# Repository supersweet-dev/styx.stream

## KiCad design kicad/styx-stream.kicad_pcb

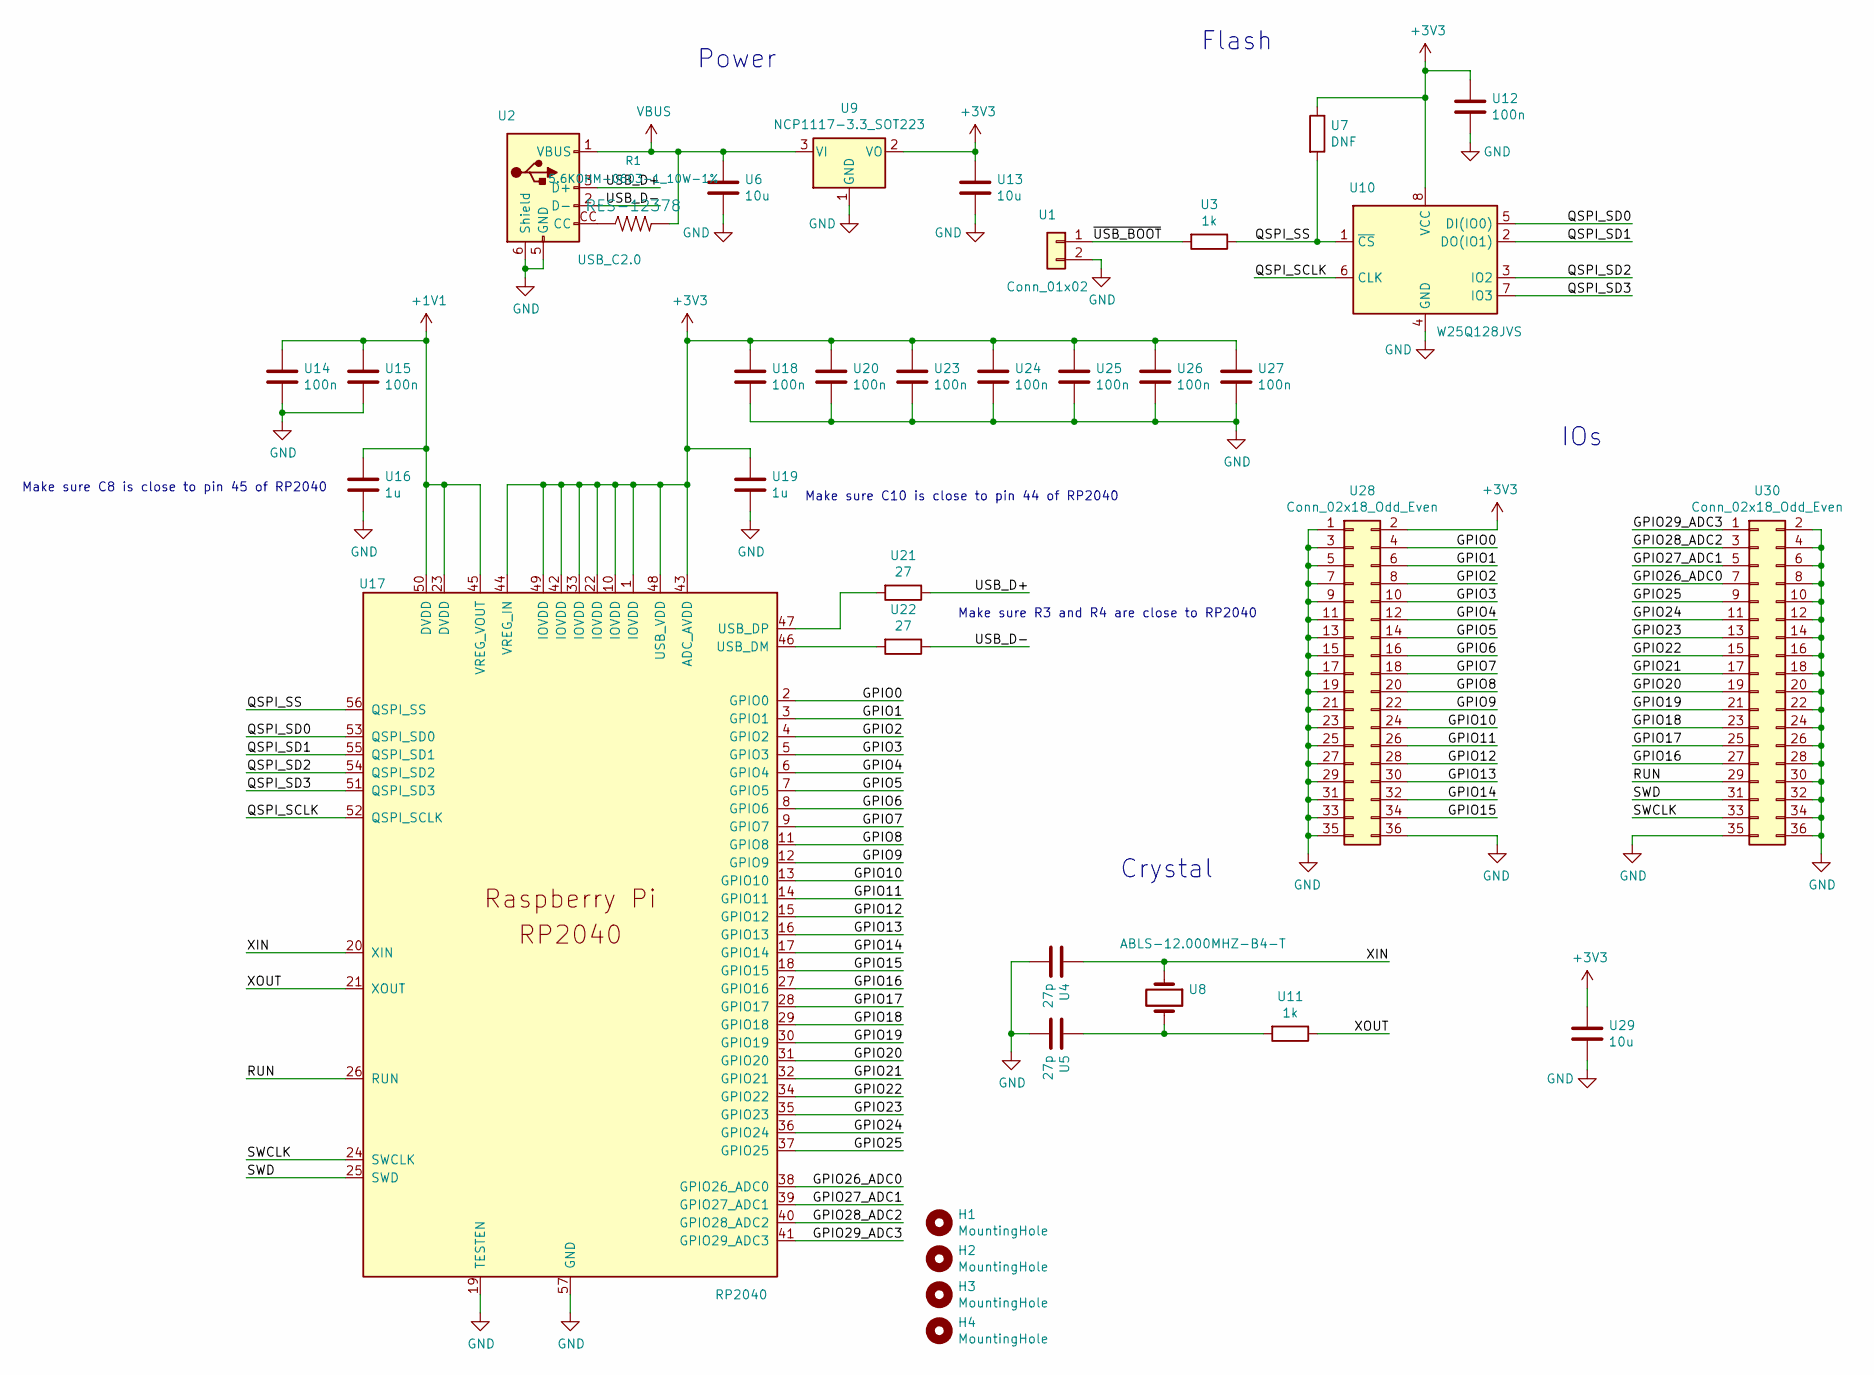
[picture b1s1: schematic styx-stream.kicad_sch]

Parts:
H1, H2, H3, H4: MountingHole; MountingHole_2.7mm_M2.5
R1: 5.6KOHM-0603-1_10W-1%; R_4020_10251Metric
U1: Conn_01x02; PinHeader_1x02_P2.54mm_Vertical
U2: USB_C2.0; USB_C_Receptacle_Amphenol_12401610E4-2A
U3, U11: 1k; C_0402_1005Metric
U4, U5: 27p; C_0402_1005Metric
U6, U13, U29: 10u; C_0805_2012Metric
U7: DNF; C_0402_1005Metric
U8: ABLS-12.000MHZ-B4-T; HC49UP
U9: NCP1117-3.3_SOT223; SOT-223-3_TabPin2
U10: W25Q128JVS; SOIC-8_5.23x5.23mm_P1.27mm
U12, U14, U15, U18, U20, U23, U24, U25, U26, U27: 100n; C_0402_1005Metric
U16, U19: 1u; C_0402_1005Metric
U17: RP2040; RP2040-QFN-56
U21, U22: 27; C_0402_1005Metric
U28, U30: Conn_02x18_Odd_Even; PinHeader_2x18_P2.54mm_Vertical

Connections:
+1V1: U14.1, U15.1, U16.1, U17.23 (DVDD), U17.45 (VREG_VOUT), U17.50 (DVDD)
+3V3: U7.1, U9.2 (VO), U10.8 (VCC), U12.1, U13.1, U17.1 (IOVDD), U17.10 (IOVDD), U17.22 (IOVDD), U17.33 (IOVDD), U17.42 (IOVDD), U17.43 (ADC_AVDD), U17.44 (VREG_IN), U17.48 (USB_VDD), U17.49 (IOVDD), U18.1, U19.1, U20.1, U23.1, U24.1, U25.1, U26.1, U27.1, U28.2, U29.1
/GPIO0: U17.2 (GPIO0), U28.4
/GPIO1: U17.3 (GPIO1), U28.6
/GPIO2: U17.4 (GPIO2), U28.8
/GPIO3: U17.5 (GPIO3), U28.10
/GPIO4: U17.6 (GPIO4), U28.12
/GPIO5: U17.7 (GPIO5), U28.14
/GPIO6: U17.8 (GPIO6), U28.16
/GPIO7: U17.9 (GPIO7), U28.18
/GPIO8: U17.11 (GPIO8), U28.20
/GPIO9: U17.12 (GPIO9), U28.22
/GPIO10: U17.13 (GPIO10), U28.24
/GPIO11: U17.14 (GPIO11), U28.26
/GPIO12: U17.15 (GPIO12), U28.28
/GPIO13: U17.16 (GPIO13), U28.30
/GPIO14: U17.17 (GPIO14), U28.32
/GPIO15: U17.18 (GPIO15), U28.34
/GPIO16: U17.27 (GPIO16), U30.27
/GPIO17: U17.28 (GPIO17), U30.25
/GPIO18: U17.29 (GPIO18), U30.23
/GPIO19: U17.30 (GPIO19), U30.21
/GPIO20: U17.31 (GPIO20), U30.19
/GPIO21: U17.32 (GPIO21), U30.17
/GPIO22: U17.34 (GPIO22), U30.15
/GPIO23: U17.35 (GPIO23), U30.13
/GPIO24: U17.36 (GPIO24), U30.11
/GPIO25: U17.37 (GPIO25), U30.9
/GPIO26_ADC0: U17.38 (GPIO26_ADC0), U30.7
/GPIO27_ADC1: U17.39 (GPIO27_ADC1), U30.5
/GPIO28_ADC2: U17.40 (GPIO28_ADC2), U30.3
/GPIO29_ADC3: U17.41 (GPIO29_ADC3), U30.1
/QSPI_SCLK: U10.6 (CLK), U17.52 (QSPI_SCLK)
/QSPI_SD0: U10.5 (DI(IO0)), U17.53 (QSPI_SD0)
/QSPI_SD1: U10.2 (DO(IO1)), U17.55 (QSPI_SD1)
/QSPI_SD2: U10.3 (IO2), U17.54 (QSPI_SD2)
/QSPI_SD3: U10.7 (IO3), U17.51 (QSPI_SD3)
/QSPI_SS: U3.1, U7.2, U10.1 (~CS), U17.56 (QSPI_SS)
/RUN: U17.26 (RUN), U30.29
/SWCLK: U17.24 (SWCLK), U30.33
/SWD: U17.25 (SWD), U30.31
/USB_D+: U2.3 (D+), U21.1
/USB_D-: U2.2 (D-), U22.1
/XIN: U4.1, U8.1, U17.20 (XIN)
/XOUT: U11.1, U17.21 (XOUT)
/~USB_BOOT: U1.1, U3.2
GND: U1.2, U2.5 (GND), U2.6 (Shield), U4.2, U5.2, U6.2, U9.1 (GND), U10.4 (GND), U12.2, U13.2, U14.2, U15.2, U16.2, U17.19 (TESTEN), U17.57 (GND), U18.2, U19.2, U20.2, U23.2, U24.2, U25.2, U26.2, U27.2, U28.1, U28.3, U28.5, U28.7, U28.9, U28.11, U28.13, U28.15, U28.17, U28.19, U28.21, U28.23, U28.25, U28.27, U28.29, U28.31, U28.33, U28.35, U28.36, U29.2, U30.2, U30.4, U30.6, U30.8, U30.10, U30.12, U30.14, U30.16, U30.18, U30.20, U30.22, U30.24, U30.26, U30.28, U30.30, U30.32, U30.34, U30.35, U30.36
unnamed: R1.1, U2.CC
unnamed: U5.1, U8.2, U11.2
unnamed: U17.46 (USB_DM), U22.2
unnamed: U17.47 (USB_DP), U21.2
VBUS: R1.2, U2.1 (VBUS), U6.1, U9.3 (VI)

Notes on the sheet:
Make sure C8 is close to pin 45 of RP2040
IOs
Flash
Make sure R3 and R4 are close to RP2040
Crystal
Make sure C10 is close to pin 44 of RP2040
Power

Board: 2 copper layers, 35 parts (0 on the bottom side), 52 nets, no tracks yet.

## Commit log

2022-11-17 init
2022-11-17 baremin
